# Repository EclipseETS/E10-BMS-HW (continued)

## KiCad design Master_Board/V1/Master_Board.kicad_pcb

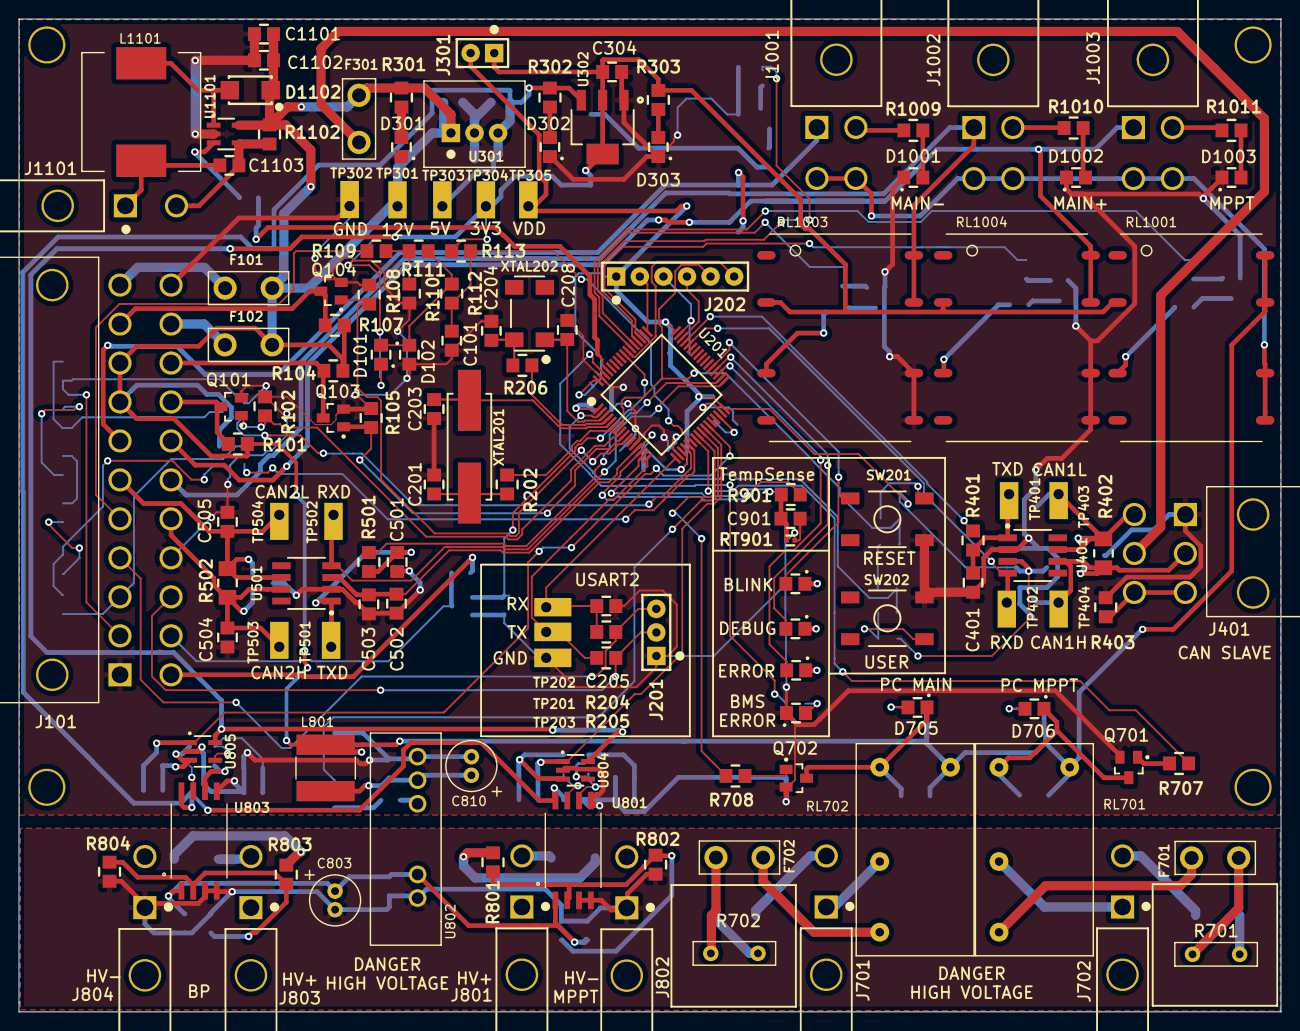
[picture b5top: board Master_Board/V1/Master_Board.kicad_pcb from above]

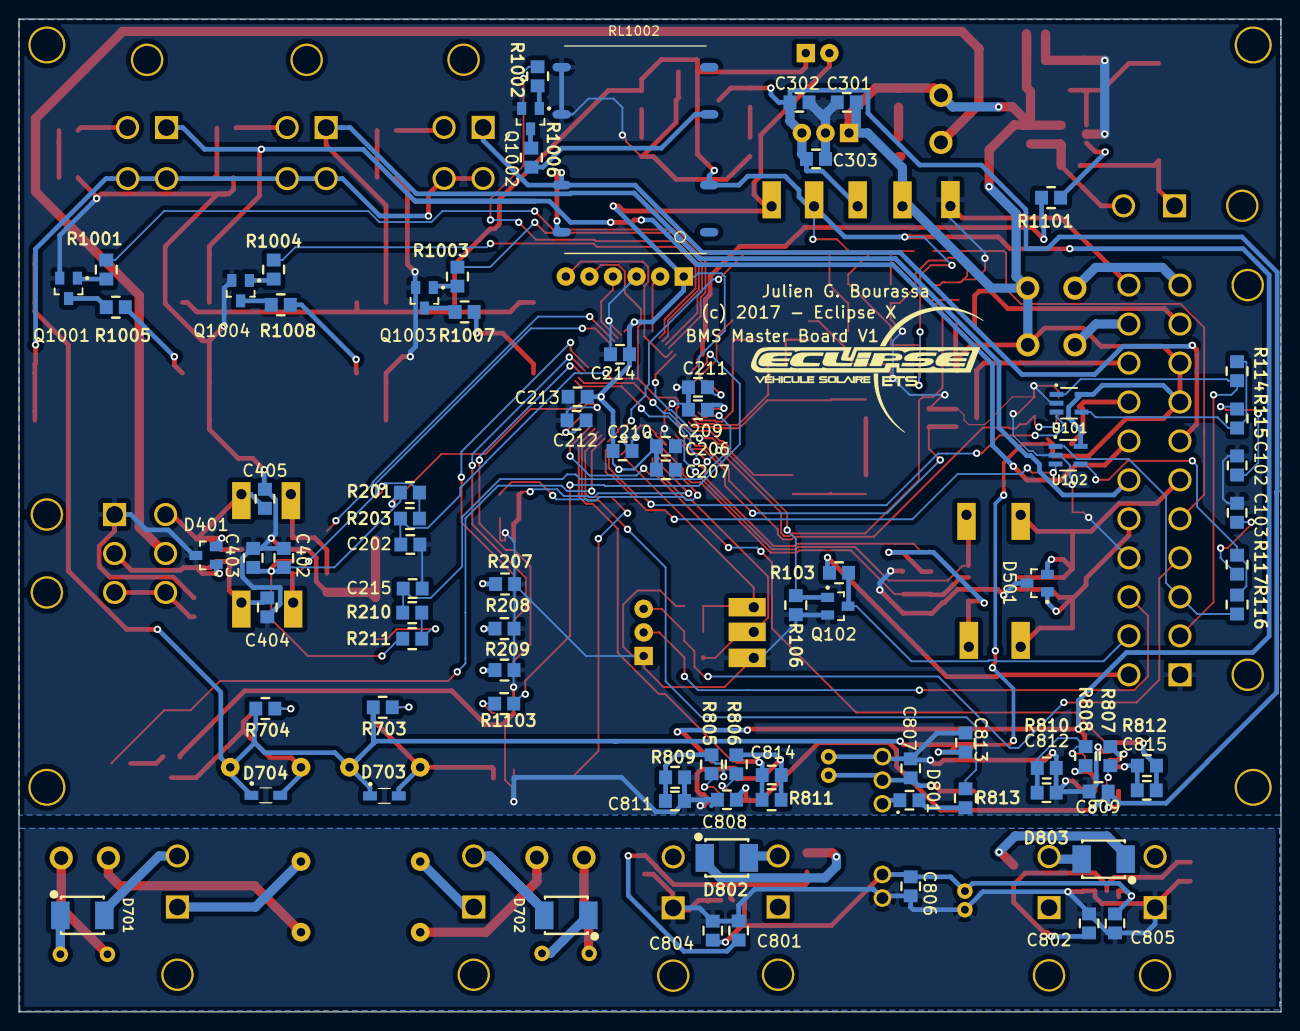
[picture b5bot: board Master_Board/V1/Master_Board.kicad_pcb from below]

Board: 2 copper layers, 136.0 x 107.0 mm, 217 parts (83 on the bottom side), 142 nets.

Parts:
C101, C207: 885012207092; C0805
C102, C103, C202, C210, C211, C213, C214, C215, C403, C503, C804, C805, C806, C807, C808, C809, C1102: 885012207098; C0805
C201, C203, C205, C404, C405, C504, C505: 885012007053; C0805
C204, C208: 885012007027; C0805
C206, C209, C402, C502, C901, C1103: 885012107015; C0805
C212, C301, C302, C1101: 885012107018; C0805
C303: 885012107014; C0805
C304: 885012107005; C0805
C401, C501, C801, C802, C811, C812, C814, C815: 885012207080; C0805
C803, C810: 860020472006; Radial-Can-5_11_2
C813: 885012207075; C0805
D101, D102, D801: SD0805S020S1R0; Diode_0805
D201, D301, D302, D303, D705, D706, D1001, D1002, D1003: 150080VS75000; LED_0805_GREEN
D202: 150080YS75000; LED_0805_YELLOW
D203, D1101: 150080RS75000; LED_0805_RED
D401, D501: D1213A-02SOL-7; SOT-23-3
D701, D702, D802, D803: NRVBS3200T3G; DO-214AA_SMB
D703, D704: NSR0530HT1G; SOD-323
D1102: B240AQ-13-F; DO-214AC_SMA
F101, F102: 39505000440; TE5_395
F301: 39511000440; TE5_395
F701, F702: 80812000440; TE5_395
J101: 649022227222
J201: Header_Male_Pin_2.54mm_1X3_,_Unshrouded; Headers_2.54mm_1X3
J202: Header_Male_Pin_2.54mm_1X6_,_Unshrouded; Headers_2.54mm_1X6
J301: Header_Male_Pin_2.54mm_1X2_,_Unshrouded; Headers_2.54mm_1X2
J401: 649006227222
J701, J702, J801, J802, J803, J804, J1101: 649002227222
J1001, J1002, J1003: 649004227222
L801: 744052471; WE-TPC-SMD
L1101: 7447715330; IND_1245
Q101, Q103, Q104: BSS806NH6327XTSA1; SOT-23-3
Q102: 2N7002P,215; SOT-23-3
Q701, Q702, Q1001, Q1002, Q1003, Q1004: BC849BLT1G; SOT-23-3
R101, R104, R107, R203, R210, R401, R501: RC0805JR-07100RL; R0805
R102, R105, R106, R108, R113: RC0805JR-07100KL; R0805
R103, R1103: RC0805JR-07330RL; R0805
R109: RC0805JR-072KL; R0805
R110: RC0805JR-07680RL; R0805
R111: RC0805JR-0710RL; R0805
R112, R205, R302, R703, R704, R1009, R1010, R1011, R1101: RC0805JR-071KL; R0805
R114, R115, R116, R117, R202, R206, R403: RC0805JR-070RL; R0805
R201, R204, R211, R301: RC0805JR-074K7L; R0805
R207, R208, R209, R303, R813: RC0805JR-07470RL; R0805
R402, R502: RC1206JR-07120RL; R1206
R701, R702: TR50JBC100R; TR50
R707, R708, R802, R804, R805, R806, R807, R808, R1001, R1002, R1003, R1004: RC0805JR-0710KL; R0805
R801, R803: RC0805JR-071ML; R0805
R809, R810, R811, R812: RC0805JR-0715KL; R0805
R901: RC0805JR-0733KL; R0805
R1005, R1006, R1007, R1008: RC0805JR-072K2L; R0805
R1102: RL0805FR-070R15L; R0805
RL701, RL702: ALQ312
RL1001, RL1002, RL1003, RL1004: CPC1907B
RT901: NCP15WB473F03RC; R0402
SW201, SW202: PTS645SM43SMTR92; PTS645_6X6X4_SMD
TP201, TP202, TP203, TP301, TP302, TP303, TP304, TP305, TP401, TP402, TP403, TP404, TP501, TP502, TP503, TP504: Test_Point_THM; Keystone_5001
U101, U102, U804, U805: LMV321RILT; SOT-23-5
U201: STM32F446RE; LQFP-64
U301: OKI-78SR-5/1.5-W36-C; OKI-78SR_Vertical
U302: AZ1117IH-3.3TRG1; SOT-223-3
U401, U501: SN65HVD232DR; SOIC-8
U801, U803: ACPL-C87A-500E; SSO-8
U802: NCS1S2405SC
U1101: AL8807W5-7; SOT-23-5
XTAL201: ABLS-8.000MHZ-D-T; HC49_US
XTAL202: ABS25-32.768KHZ-6-T; ABS25

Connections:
3.3V: C304.2, D101.1, J301.1, R113.1, R303.2, RL1001.2, RL1002.2, RL1003.2, RL1004.2, TP304.1, U302.2, U302.4, U804.5, U805.5
5V: C302.2, C303.2, C808.2, C809.2, R302.2, TP303.1, U301.3, U302.3, U801.8, U803.8
12V: C301.2, C813.1, C1101.1, C1102.1, D703.1, D704.1, D1102.1, F101.2, F102.2, F301.2, J101.8, J101.9, L801.2, R101.1, R104.1, R107.1, R301.2, R703.1, R704.1, R1102.1, RL701.1, RL702.1, RL1001.7, RL1001.8, TP301.1, U101.5, U102.5, U301.1, U1101.5
/12V_IN1: F101.1, J101.11
/12V_IN2: F102.1, J101.21
/ANA1: J101.2, R114.1, U101.1
/ANA2: J101.3, R116.2, U102.1
/ANA_IN: J101.5, R109.1
/ANA_SUP: J101.12, R103.1
/CAN1/CAN_N: C404.1, D401.1, J401.2, R402.2, TP404.1, U401.6
/CAN1/CAN_P: C405.1, D401.2, J401.4, R402.1, TP403.1, U401.7
/CAN1/Shield1: J401.3, J401.6, R403.1
/CAN1_RX: TP402.1, U201.44, U401.4
/CAN1_TX: R401.1, U201.45
/CAN2_H: C504.1, D501.1, J101.16, R502.1, TP503.1, U501.7
/CAN2_L: C505.1, D501.2, J101.6, R502.2, TP504.1, U501.6
/CAN2_RX: TP502.1, U201.33, U501.4
/CAN2_TX: R501.1, U201.34
/IO1: J101.17, J1002.1, RL1003.7, RL1003.8
/IO2: J101.7, J1001.1, RL1002.7, RL1002.8
/IO3: J101.18, J1003.1, RL1004.7, RL1004.8
/IO5: J101.19, Q101.3, R101.2
/IO7: J101.20, Q103.3, R104.2
/IO8: J101.10, Q104.3, R107.2
/Isolated/VoltageSense/5V_ISO: C803.1, C804.2, C805.2, C806.1, U801.1, U802.6, U803.1
/Isolated/VoltageSense/BP-HV+: D803.1, R803.1
/Isolated/VoltageSense/MPPT-HV+: D802.1, R801.1
/NRST: C202.1, J202.5, R203.2, U201.7
/NTC_1_ADC: C901.1, R901.1, RT901.2, U201.15
/NTC_1_GPIO: R901.2, U201.14
/PA4: U101.3, U201.20
/PA5: U102.3, U201.21
/PA6: C101.1, R112.2, R113.2, U201.22
/PA7: R707.2, U201.23
/PB0: C814.1, R811.2, U201.26, U804.1
/PB1: C815.1, R812.2, U201.27, U805.1
/PB4: Q102.1, R106.2, U201.56
/PB8: R1101.2, U201.61
/PB9: R1103.2, U201.62
/PB14: D203.2, U201.35
/PB15: D202.2, U201.36
/PC0: Q101.1, R102.2, U201.8
/PC1: Q103.1, R105.2, U201.9
/PC2: Q104.1, R108.2, U201.10
/PC4: R708.2, U201.24
/PC5: R813.2, U201.25
/PC6: D201.2, U201.37
/PC10: R1004.1, U201.51
/PC11: R1002.1, U201.52
/PC12: R1003.1, U201.53
/PD2: R1001.1, U201.54
/PWM2_OUT: J101.13, Q102.3, R103.2
/RS232_RX: J101.4, J201.3, R204.1
/RS232_TX: J101.14, J201.2, R205.1
/STM32F446/PA2_TX: R205.2, TP201.1, U201.16
/STM32F446/PA3_RX: C205.2, R204.2, TP202.1, U201.17
/STM32F446/SWCLK: J202.2, U201.49
/STM32F446/SWDIO: J202.4, U201.46
/STM32F446/SWO: J202.6, U201.55
/STM32F446/USER_BTN: C215.1, R210.2, U201.2
/VBat: C209.2, U201.1
CAN_PWR: F301.1, J401.5
DGND: C101.2, C102.2, C103.2, C201.1, C202.2, C203.2, C204.1, C205.1, C206.1, C207.1, C208.2, C209.1, C210.2, C211.1, C212.1, C213.2, C214.2, C215.2, C301.1, C302.1, C303.1, C304.1, C401.1, C402.1, C403.1, C404.2, C405.2, C501.2, C502.1, C503.1, C504.2, C505.2, C801.2, C802.2, C803.2, C804.1, C805.1, C806.2, C807.2, C808.1, C809.1, C810.2, C811.1, C812.1, C813.2, C901.2, C1101.2, C1102.2, D102.2, D301.1, D302.1, D303.1, D401.3, D501.3, D1001.1, D1002.1, D1003.1, D1101.1, J101.1, J101.15, J101.22, J201.1, J202.3, J401.1, J802.1, J804.1, Q101.2, Q102.2, Q103.2, Q104.2, Q701.2, Q702.2, Q1001.2, Q1002.2, Q1003.2, Q1004.2, R102.1, R105.1, R106.1, R108.1, R110.2, R207.1, R208.1, R209.1, R403.2, R802.2, R804.2, R809.2, R810.2, RL1002.5, RL1002.6, RL1003.5, RL1003.6, RL1004.5, RL1004.6, RT901.1, SW201.4, SW202.3, TP203.1, TP302.1, U101.2, U102.2, U201.12, U201.18, U201.31, U201.47, U201.63, U301.2, U302.1, U401.2, U501.2, U801.3, U801.4, U801.5, U802.1, U802.7, U803.3, U803.4, U803.5, U804.2, U805.2, U1101.2
unnamed: C102.1, R115.2
unnamed: C103.1, R117.1
unnamed: C201.2, R202.2, XTAL201.1
unnamed: C203.1, U201.5, XTAL201.2
unnamed: C204.2, R206.2, XTAL202.4
unnamed: C208.1, U201.3, XTAL202.1
unnamed: C212.2, U201.30
unnamed: C401.2, R401.2, TP401.1, U401.1
unnamed: C501.1, R501.2, TP501.1, U501.1
unnamed: C801.1, R801.2, R802.1, U801.2
unnamed: C802.1, R803.2, R804.1, U803.2
unnamed: C807.1, C810.1, L801.1, U802.2
unnamed: C811.2, R806.2, R809.1, U804.4
unnamed: C812.2, R808.2, R810.1, U805.4
unnamed: C814.2, R805.2, R811.1, U804.3
unnamed: C815.2, R807.2, R812.1, U805.3
unnamed: C1103.1, J1101.2, R1102.2, U1101.4
unnamed: C1103.2, J1101.1, L1101.2
unnamed: D101.2, D102.1, R111.2, R112.1
unnamed: D201.1, R207.2
unnamed: D202.1, R208.2
unnamed: D203.1, R209.2
unnamed: D301.2, R301.1
unnamed: D302.2, R302.1
unnamed: D303.2, R303.1
unnamed: D701.1, R701.1
unnamed: D701.2, J702.2
unnamed: D702.1, R702.1
unnamed: D702.2, J701.2
unnamed: D703.2, D705.1, Q702.3, RL702.2
unnamed: D704.2, D706.1, Q701.3, RL701.2
unnamed: D705.2, R703.2
unnamed: D706.2, R704.2
unnamed: D801.1, U802.3
unnamed: D801.2, R813.1
unnamed: D802.2, J801.2
unnamed: D803.2, J803.2
unnamed: D1001.2, R1009.2
unnamed: D1002.2, R1010.2
unnamed: D1003.2, R1011.2
unnamed: D1101.2, R1103.1
unnamed: D1102.2, L1101.1, U1101.1
unnamed: F701.1, R701.2
unnamed: F701.2, RL701.4
unnamed: F702.1, R702.2
unnamed: F702.2, RL702.4
unnamed: J701.1, RL702.3
unnamed: J702.1, RL701.3
unnamed: J1001.2, R1009.1
unnamed: J1001.3, J1001.4, J1002.3, J1002.4, J1003.3, J1003.4, RL1001.5, RL1001.6
unnamed: J1002.2, R1010.1
unnamed: J1003.2, R1011.1
unnamed: Q701.1, R707.1
unnamed: Q702.1, R708.1
unnamed: Q1001.1, R1001.2
unnamed: Q1001.3, R1005.1
unnamed: Q1002.1, R1002.2
unnamed: Q1002.3, R1006.1
unnamed: Q1003.1, R1003.2
unnamed: Q1003.3, R1007.1
unnamed: Q1004.1, R1004.2
unnamed: Q1004.3, R1008.1
unnamed: R109.2, R110.1, R111.1
unnamed: R114.2, R115.1, U101.4
unnamed: R116.1, R117.2, U102.4
unnamed: R201.1, R203.1, SW201.2
unnamed: R202.1, U201.6
unnamed: R206.1, U201.4
unnamed: R210.1, R211.1, SW202.1
unnamed: R805.1, U801.7
unnamed: R806.1, U801.6
unnamed: R807.1, U803.7
unnamed: R808.1, U803.6
unnamed: R1005.2, RL1001.3
unnamed: R1006.2, RL1002.3
unnamed: R1007.2, RL1003.3
unnamed: R1008.2, RL1004.3
unnamed: R1101.1, U1101.3
VDD: C206.2, C207.2, C210.1, C211.2, C213.1, C214.1, C402.2, C403.2, C502.2, C503.2, J202.1, J301.2, R201.2, R211.2, TP305.1, U201.13, U201.19, U201.32, U201.48, U201.64, U401.3, U501.3

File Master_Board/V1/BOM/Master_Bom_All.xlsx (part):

Component | References | Description | Manufacturer | Manufacturer Part Number | Supplier | Supplier Part Number | Quantity Per PCB | Footprint
1 | C803 C810 | CAP ALUM 47UF 20% 25V RADIAL | Wurth Electronics Inc. | 860020472006 | Digikey | 732-8823-1-ND | 2 | Radial-Can-5_11_2
2 | C204 C208 | CAP CER 6.8PF 25V C0G/NP0 0805 | Wurth Electronics Inc. | 885012007027 | Digikey | 732-7826-1-ND | 2 | C0805
3 | C201 C203 C205 C404 C405 C504 C505 | CAP CER 22PF 50V C0G/NP0 0805 | Wurth Electronics Inc. | 885012007053 | Digikey | 732-7848-1-ND | 7 | C0805
4 | C304 | CAP CER 22UF 6.3V X5R 0805 | Wurth Electronics Inc. | 885012107005 | Digikey | 732-7616-1-ND | 1 | C0805
5 | C303 | CAP CER 10UF 16V X5R 0805 | Wurth Electronics Inc. | 885012007027 | Digikey | 732-7624-1-ND | 1 | C0805
6 | C206 C209 C402 C502 C901 C1103 | CAP CER 1UF 25V X5R 0805 | Wurth Electronics Inc. | 885012107015 | Digikey | 732-7625-1-ND | 6 | C0805
7 | C212 C301 C302 C1101 | CAP CER 4.7UF 25V X5R 0805 | Wurth Electronics Inc. | 885012107018 | Digikey | 732-7628-1-ND | 4 | C0805
8 | C813 | CAP CER 0.33UF 25V X7R 0805 | Wurth Electronics Inc. | 885012207075 | Digikey | 732-7669-1-ND | 1 | C0805
9 | C401 C501 C801 C802 C811 C812 C814 C815 | CAP CER 100PF 50V X7R 0805 | Wurth Electronics Inc. | 885012207080 | Digikey | 732-8062-1-ND | 8 | C0805
10 | C101 C207 | CAP CER 10000PF 50V X7R 0805 | Wurth Electronics Inc. | 885012207092 | Digikey | 732-8074-1-ND | 2 | C0805
11 | C102 C103 C202 C210 C211 C213 C214 C215 C403 C503 C804 C805 C806 C807 C808 C809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 | CAP CER 0.1UF 50V X7R 0805 | Wurth Electronics Inc. | 885012207098 | Digikey | 732-8080-1-ND | 17 | C0805
12 | D203 D1101 | LED RED CLEAR 0805 SMD | Wurth Electronics Inc. | 150080RS75000 | Digikey | 732-4984-1-ND | 2 | LED_0805_RED
13 | D201 D301 D302 D303 D705 D706 D1001 D1002 D1003 | LED GREEN CLEAR 0805 SMD | Wurth Electronics Inc. | 150080VS75000 | Digikey | 732-4986-1-ND | 9 | LED_0805_GREEN
14 | D202 | LED YELLOW CLEAR 0805 SMD | Wurth Electronics Inc. | 150080YS75000 | Digikey | 732-4987-1-ND | 1 | LED_0805_YELLOW
15 | D1102 | DIODE SCHOTTKY 40V 2A SMA | Diode Incorporated | B240AQ-13-F | Digikey | B240AQ-13-FDICT-ND | 1 | DO-214AC_SMA
16 | D401 D501 | TVS DIODE 3.3VWM 10VC SOT23 | Diodes Incorporated | D1213A-02SOL-7 | Digikey | D1213A-02SOL-7DICT-ND | 2 | SOT-23-3
17 | D701 D702 D802 D803 | DIODE SCHOTTKY 200V 3A SMB | ON Semiconductor | NRVBS3200T3G | Digikey | NRVBS3200T3GOSCT-ND | 4 | DO-214AA_SMB
18 | D703 D704 | DIODE SCHOTTKY 30V 500MA SOD323 | ON Semiconductor | NSR0530HT1G | Digikey | NSR0530HT1GOSCT-ND | 2 | SOD-323
19 | D101 D102 D801 | DIODE SCHOTTKY 20V 1A 0805 | AVX Corporation | SD0805S020S1R0 | Digikey | 478-7800-1-ND | 3 | Diode_0805
20 | F101 F102 | FUSE BOARD MNT 1A 125VAC RADIAL | Littelfuse Inc. | 39505000440 | Digikey | WK4341BK-ND | 2 | TE5_395
21 | F301 | FUSE HOLDER RADIAL 250V 6.3A PCB | Littelfuse Inc. | 56200001009 | Digikey | WK0009-ND | 1 | TE5_395
22 | F701 F702 | FUSE BOARD MNT 2A 250VAC 450VDC | Littelfuse Inc. | 80812000440 | Digikey | WK6289-ND | 2 | TE5_395
23 | J701 J702 J801 J802 J803 J804 J1101 | HEADER MALE DUAL ANGLE W/MNT 2P | Wurth Electronics Inc. | 649002227222 | Digikey | 732-1937-ND | 7 | 649002227222
24 | J1001 J1002 J1003 | HEADER MALE DUAL ANGLE W/MNT 4P | Wurth Electronics Inc. | 649004227222 | Digikey | 732-1938-ND | 3 | 649004227222
25 | J401 | HEADER MALE DUAL ANGLE W/MNT 6P | Wurth Electronics Inc. | 649006227222 | Digikey | 732-1939-ND | 1 | 649006227222
26 | J101 | HEADER MALE DUAL ANGLE W/MNT 22P | Wurth Electronics Inc. | 649022227222 | Digikey | 732-4785-ND | 1 | 649022227222
27 | J301 | Pin Male Single Row Pin Header Strip | Manufacturer | Manufacturer Part Number | Ebay | Pin Male Single Row Pin Header Strip | 1 | Headers_2.54mm_1X2
28 | J201 | Pin Male Single Row Pin Header Strip | Manufacturer | Manufacturer Part Number | Ebay | Pin Male Single Row Pin Header Strip | 1 | Headers_2.54mm_1X3
29 | J202 | Pin Male Single Row Pin Header Strip | Manufacturer | Manufacturer Part Number | Ebay | Pin Male Single Row Pin Header Strip | 1 | Headers_2.54mm_1X6
30 | L801 | FIXED IND 470UH 140MA 5.5 OHM | Wurth Electronics Inc. | 744052471 | Digikey | 732-3668-1-ND | 1 | WE-TPC-SMD
31 | L1101 | FIXED IND 33UH 2.3A 85 MOHM SMD | Wurth Electronics Inc. | 7447715330 | Digikey | 732-2196-6-ND | 1 | IND_1245
32 | Q102 | MOSFET N-CH 60V 0.36A SOT-23 | Nexperia USA Inc. | 2N7002P,215 | Digikey | 1727-4692-1-ND | 1 | SOT-23-3
33 | Q701 Q702 Q1001 Q1002 Q1003 Q1004 | TRANS NPN 30V 0.1A SOT-23 | ON Semiconductor | BC849BLT1G | Digikey | BC849BLT1GOSCT-ND | 6 | SOT-23-3
34 | Q101 Q103 Q104 | MOSFET N-CH 20V 2.3A SOT23 | Infineon Technologies | BSS806NH6327XTSA1 | Digikey | BSS806NH6327XTSA1CT-ND | 3 | SOT-23-3
35 | R114 R115 R116 R117 R202 R206 R403 | RES SMD 0.0 OHM JUMPER 1/8W 0805 | Yageo | RC0805JR-070RL | Digikey | 311-0.0ARCT-ND | 7 | R0805
36 | R102 R105 R106 R108 R113 | RES SMD 100K OHM 5% 1/8W 0805 | Yageo | RC0805JR-07100KL | Digikey | 311-100KARCT-ND | 5 | R0805
37 | R101 R104 R107 R203 R210 R401 R501 | RES SMD 100 OHM 5% 1/8W 0805 | Yageo | RC0805JR-07100RL | Digikey | 311-100ARCT-ND | 7 | R0805
38 | R707 R708 R802 R804 R805 R806 R807 R808 R1001 R1002 R1003 R1004 | RES SMD 10K OHM 5% 1/8W 0805 | Yageo | RC0805JR-0710KL | Digikey | 311-10KARCT-ND | 12 | R0805
39 | R111 | RES SMD 10 OHM 5% 1/8W 0805 | Yageo | RC0805JR-0710RL | Digikey | 311-10ARCT-ND | 1 | R0805
40 | R809 R810 R811 R812 | RES SMD 15K OHM 5% 1/8W 0805 | Yageo | RC0805JR-0715KL | Digikey | 311-15KARTR-ND | 4 | R0805
41 | R112 R205 R302 R703 R704 R1009 R1010 R1011 R1101 | RES SMD 1K OHM 5% 1/8W 0805 | Yageo | RC0805JR-071KL | Digikey | 311-1.0KARCT-ND | 9 | R0805
42 | R801 R803 | RES SMD 1M OHM 5% 1/8W 0805 | Yageo | RC0805JR-071ML | Digikey | 311-1.0MARCT-ND | 2 | R0805
43 | R1005 R1006 R1007 R1008 | RES SMD 2.2K OHM 5% 1/8W 0805 | Yageo | RC0805JR-072K2L | Digikey | 311-2.2KARCT-ND | 4 | R0805
44 | R109 | RES SMD 2K OHM 5% 1/8W 0805 | Yageo | RC0805JR-072KL | Digikey | 311-2.0KARCT-ND | 1 | R0805
45 | R103 R1103 | RES SMD 330 OHM 5% 1/8W 0805 | Yageo | RC0805JR-07330RL | Digikey | 311-330ARCT-ND | 2 | R0805
46 | R901 | RES SMD 33K OHM 5% 1/8W 0805 | Yageo | RC0805JR-0733KL | Digikey | 311-33KARCT-ND | 1 | R0805
47 | R207 R208 R209 R303 R813 | RES SMD 470 OHM 5% 1/8W 0805 | Yageo | RC0805JR-07470RL | Digikey | 311-470ARCT-ND | 5 | R0805
48 | R201 R204 R211 R301 | RES SMD 4.7K OHM 5% 1/8W 0805 | Yageo | RC0805JR-074K7L | Digikey | 311-4.7KARCT-ND | 4 | R0805
49 | R110 | RES SMD 680 OHM 5% 1/8W 0805 | Yageo | RC0805JR-07680RL | Digikey | 311-680ARCT-ND | 1 | R0805
50 | R402 R502 | RES SMD 120 OHM 5% 1/4W 1206 | Yageo | RC1206JR-07120RL | Digikey | 311-120ERCT-ND | 2 | R1206
51 | R1102 | RES SMD 0.15 OHM 1% 1/8W 0805 | Yageo | RL0805FR-070R15L | Digikey | 311-.15SCT-ND | 1 | R0805
52 | R701 R702 | RES 100 OHM 50W 5% TO220 | Stackpole Electronics Inc. | TR50JBC100R | Digikey | TR50JBC100R-ND | 2 | TR50
53 | RL701 RL702 | RELAY GEN PURPOSE SPST 10A 12V | Panasonic Electric Works | ALQ312 | Digikey | 255-3556-ND | 2 | ALQ312
54 | RL1001 RL1002 RL1003 RL1004 | RELAY OPTOMOS SP-NO 6A 8-SOP | IXYS Integrated Circuits Division | CPC1907B | Digikey | CLA394-ND | 4 | CPC1907B
55 | RT901 | NTC THERMISTOR 47K OHM 1% 0402 | Murata Electronics North America | NCP15WB473F03RC | Digikey | 490-4802-1-ND | 1 | R0402
56 | SW201 SW202 | SWITCH TACTILE SPST-NO 0.05A 12V | C&K | PTS645SM43SMTR92 LFS | Digikey | CKN9112CT-ND | 2 | PTS645_6X6X4_SMD
57 | U801 U803 | Precision Optically Isolated Voltage Sensor | Broadcom Limited | ACPL-C87A-500E | Digikey | 516-3140-1-ND | 2 | SSO-8
58 | U1101 | IC LED DRVR REG PWM 1A TSOT25 | Diodes Incorporated | AL8808WT-7 | Digikey | AL8808WT-7DICT-ND | 1 | SOT-23-5
59 | U302 | IC REG LDO 3.3V 0.8A SOT223 | Diodes Incorporated | AZ1117IH-3.3TRG1 | Digikey | AZ1117IH-3.3TRG1DICT-ND | 1 | SOT-223-3
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
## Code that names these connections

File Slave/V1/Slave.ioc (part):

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Mcu.Name=STM32F446R(C-E)Tx
Mcu.Package=LQFP64
Mcu.UserName=STM32F446RETx
PA0-WKUP.GPIOParameters=GPIO_Label
PA0-WKUP.GPIO_Label=NTC_1_ADC
PA0-WKUP.Signal=ADCx_IN0
PA1.GPIOParameters=GPIO_Label
PA1.GPIO_Label=NTC_1_EN
PA1.Signal=GPIO_Output
PA10.GPIOParameters=GPIO_Label
PA10.GPIO_Label=CS_8
PA10.Signal=GPIO_Output
PA13.GPIOParameters=GPIO_Label
PA13.GPIO_Label=TMS
PA13.Signal=SYS_JTMS-SWDIO
PA14.GPIOParameters=GPIO_Label
PA14.GPIO_Label=TCK
PA14.Signal=SYS_JTCK-SWCLK
PA15.GPIOParameters=GPIO_Label
PA15.GPIO_Label=DE_1
PA15.Signal=GPIO_Output
PA2.GPIOParameters=GPIO_Label
PA2.GPIO_Label=USART_TX
PA2.Mode=Asynchronous
PA2.Signal=USART2_TX
PA3.GPIOParameters=GPIO_Label
PA3.GPIO_Label=USART_RX
PA3.Mode=Asynchronous
PA3.Signal=USART2_RX
PA5.GPIOParameters=GPIO_Label
PA5.GPIO_Label=LED_BLINK
PA5.Signal=GPIO_Output
PA6.GPIOParameters=GPIO_Label
PA6.GPIO_Label=LED_DEBUG
PA6.Signal=GPIO_Output
PA7.GPIOParameters=GPIO_Label
PA7.GPIO_Label=LED_ERROR
PA7.Signal=GPIO_Output
PA8.GPIOParameters=GPIO_Label
PA8.GPIO_Label=POWER_EN
PA8.Signal=GPIO_Output
PA9.GPIOParameters=GPIO_Label
PA9.GPIO_Label=DE_8
PA9.Signal=GPIO_Output
PB0.GPIOParameters=GPIO_Label
PB0.GPIO_Label=NTC_2_EN
PB0.Signal=GPIO_Output
PB1.GPIOParameters=GPIO_Label
PB1.GPIO_Label=NTC_2_ADC
PB1.Signal=ADCx_IN9
PB10.GPIOParameters=GPIO_Label
PB10.GPIO_Label=CS_5
PB10.Signal=GPIO_Output
PB12.GPIOParameters=GPIO_Label
PB12.GPIO_Label=DE_6
PB12.Signal=GPIO_Output
PB13.GPIOParameters=GPIO_Label
PB13.GPIO_Label=CS_6
PB13.Signal=GPIO_Output
PB14.GPIOParameters=GPIO_Label
PB14.GPIO_Label=DE_7
PB14.Signal=GPIO_Output
PB15.GPIOParameters=GPIO_Label
PB15.GPIO_Label=CS_7
PB15.Signal=GPIO_Output
PB2.GPIOParameters=GPIO_Label
PB2.GPIO_Label=DE_5
PB2.Signal=GPIO_Output
PB3.GPIOParameters=GPIO_Label
PB3.GPIO_Label=SWO
PB3.Signal=SYS_JTDO-SWO
PB4.GPIOParameters=GPIO_Label
PB4.GPIO_Label=CS_2
PB4.Signal=GPIO_Output
PB6.GPIOParameters=GPIO_Label
PB6.GPIO_Label=BALANCING_PWM_5
PB6.Signal=S_TIM4_CH1
PB7.GPIOParameters=GPIO_Label
PB7.GPIO_Label=BALANCING_PWM_6
PB7.Signal=S_TIM4_CH2
PB8.GPIOParameters=GPIO_Label
PB8.GPIO_Label=BALANCING_PWM_7
PB8.Signal=S_TIM4_CH3
PB9.GPIOParameters=GPIO_Label
PB9.GPIO_Label=BALANCING_PWM_8
PB9.Signal=S_TIM4_CH4
PC0.GPIOParameters=GPIO_Label
PC0.GPIO_Label=DE_3
PC0.Signal=GPIO_Output
PC1.GPIOParameters=GPIO_Label
PC1.GPIO_Label=CS_3
PC1.Signal=GPIO_Output
PC10.Mode=RX_Only_Simplex_Unidirect_Master
PC10.Signal=SPI3_SCK
PC11.Mode=RX_Only_Simplex_Unidirect_Master
PC11.Signal=SPI3_MISO
PC12.GPIOParameters=GPIO_Label
PC12.GPIO_Label=CS_1
PC12.Signal=GPIO_Output
PC13.GPIOParameters=GPIO_Label,GPIO_ModeDefaultEXTI
PC13.GPIO_Label=BTN_USER
PC13.GPIO_ModeDefaultEXTI=GPIO_MODE_EVT_RISING
PC13.Signal=GPXTI13
PC14-OSC32_IN.Signal=RCC_OSC32_IN
PC15-OSC32_OUT.Signal=RCC_OSC32_OUT
PC2.GPIOParameters=GPIO_Label
PC2.GPIO_Label=DE_4
PC2.Signal=GPIO_Output
PC3.GPIOParameters=GPIO_Label
PC3.GPIO_Label=CS_4
PC3.Signal=GPIO_Output
PC6.GPIOParameters=GPIO_Label
PC6.GPIO_Label=BALANCING_PWM_1
PC6.Signal=S_TIM8_CH1
PC7.GPIOParameters=GPIO_Label
PC7.GPIO_Label=BALANCING_PWM_2
PC7.Signal=S_TIM8_CH2
PC8.GPIOParameters=GPIO_Label
PC8.GPIO_Label=BALANCING_PWM_3
PC8.Signal=S_TIM8_CH3
PC9.GPIOParameters=GPIO_Label
PC9.GPIO_Label=BALANCING_PWM_4
PC9.Signal=S_TIM8_CH4
PD2.GPIOParameters=GPIO_Label
PD2.GPIO_Label=DE_2
PD2.Signal=GPIO_Output
PH0-OSC_IN.Mode=HSE-External-Oscillator
PH0-OSC_IN.Signal=RCC_OSC_IN
PH1-OSC_OUT.Mode=HSE-External-Oscillator
PH1-OSC_OUT.Signal=RCC_OSC_OUT
RCC.HSE_VALUE=8000000
RCC.SYSCLKFreq_VALUE=180000000
RCC.SYSCLKSource=RCC_SYSCLKSOURCE_PLLCLK
board=NUCLEO-F446RE
boardIOC=true

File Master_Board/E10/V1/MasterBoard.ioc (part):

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Mcu.Name=STM32F446R(C-E)Tx
Mcu.Package=LQFP64
Mcu.UserName=STM32F446RETx
PA0-WKUP.Signal=GPIO_Output
PA1.Signal=ADCx_IN1
PA11.Mode=Master
PA11.Signal=CAN1_RX
PA12.Mode=Master
PA12.Signal=CAN1_TX
PA13.Signal=SYS_JTMS-SWDIO
PA14.Signal=SYS_JTCK-SWCLK
PA2.Signal=USART2_TX
PA3.Signal=USART2_RX
PA4.Signal=COMP_DAC1_group
PA5.Signal=COMP_DAC2_group
PA6.Signal=ADCx_IN6
PA7.Signal=GPIO_Output
PB0.Signal=ADCx_IN8
PB1.Signal=ADCx_IN9
PB12.Mode=Slave
PB12.Signal=CAN2_RX
PB13.Mode=Slave
PB13.Signal=CAN2_TX
PB14.Signal=GPIO_Output
PB15.Signal=GPIO_Output
PB3.Signal=SYS_JTDO-SWO
PB4.Signal=S_TIM3_CH1
PB8.Signal=S_TIM10_CH1
PB9.Signal=GPIO_Output
PC0.Signal=GPIO_Output
PC1.Signal=GPIO_Output
PC10.Signal=GPIO_Output
PC11.Signal=GPIO_Output
PC12.Signal=GPIO_Output
PC13.Signal=GPIO_Input
PC14-OSC32_IN.Signal=RCC_OSC32_IN
PC15-OSC32_OUT.Signal=RCC_OSC32_OUT
PC2.Signal=GPIO_Output
PC4.Signal=GPIO_Output
PC5.Signal=GPIO_Output
PC6.Signal=GPIO_Output
PD2.Signal=GPIO_Output
PH0-OSC_IN.Signal=RCC_OSC_IN
PH1-OSC_OUT.Signal=RCC_OSC_OUT

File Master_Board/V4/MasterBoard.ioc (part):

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Mcu.Name=STM32F446R(C-E)Tx
Mcu.Package=LQFP64
Mcu.UserName=STM32F446RETx
PA0-WKUP.GPIOParameters=GPIO_Label
PA0-WKUP.GPIO_Label=NTC_1_GPIO
PA0-WKUP.Signal=GPIO_Output
PA1.GPIOParameters=GPIO_Label
PA1.GPIO_Label=NTC_1_ADC
PA1.Signal=ADCx_IN1
PA10.Mode=Asynchronous
PA10.Signal=USART1_RX
PA11.Mode=Master
PA11.Signal=CAN1_RX
PA12.Mode=Master
PA12.Signal=CAN1_TX
PA13.Signal=SYS_JTMS-SWDIO
PA14.Signal=SYS_JTCK-SWCLK
PA2.Mode=Asynchronous
PA2.Signal=USART2_TX
PA3.Mode=Asynchronous
PA3.Signal=USART2_RX
PA4.GPIOParameters=GPIO_Label
PA4.GPIO_Label=VSENSE_BP
PA4.Signal=ADCx_IN4
PA5.GPIOParameters=GPIO_Label
PA5.GPIO_Label=VSENSE_EN
PA5.Signal=GPIO_Output
PA6.GPIOParameters=GPIO_Label
PA6.GPIO_Label=VSENSE_MPPT
PA6.Signal=ADCx_IN6
PA9.Mode=Asynchronous
PA9.Signal=USART1_TX
PB10.GPIOParameters=GPIO_Label
PB10.GPIO_Label=PC_MAIN
PB10.Signal=GPIO_Output
PB12.GPIOParameters=GPIO_Label
PB12.GPIO_Label=LEDDRIVER_ERROR
PB12.Signal=GPIO_Output
PB13.Mode=Slave
PB13.Signal=CAN2_TX
PB14.GPIOParameters=GPIO_Label
PB14.GPIO_Label=LED_ASSERT
PB14.Signal=GPIO_Output
PB15.GPIOParameters=GPIO_Label
PB15.GPIO_Label=LED_DEBUG
PB15.Signal=GPIO_Output
PB2.GPIOParameters=GPIO_Label
PB2.GPIO_Label=PC_MPPT
PB2.Signal=GPIO_Output
PB3.Signal=SYS_JTDO-SWO
PB5.Mode=Slave
PB5.Signal=CAN2_RX
PC0.GPIOParameters=GPIO_Label
PC0.GPIO_Label=GPO1_EN
PC0.Signal=GPIO_Output
PC1.GPIOParameters=GPIO_Label
PC1.GPIO_Label=GP02_EN
PC1.Signal=GPIO_Output
PC10.GPIOParameters=GPIO_Label
PC10.GPIO_Label=CONTACTOR_MPPT
PC10.Signal=GPIO_Output
PC11.GPIOParameters=GPIO_Label
PC11.GPIO_Label=CONTACTOR_MAINN
PC11.Signal=GPIO_Output
PC12.GPIOParameters=GPIO_Label
PC12.GPIO_Label=CONTACTOR_MAINP
PC12.Signal=GPIO_Output
PC14-OSC32_IN.Signal=RCC_OSC32_IN
PC15-OSC32_OUT.Signal=RCC_OSC32_OUT
PC2.GPIOParameters=GPIO_Label
PC2.GPIO_Label=GPO3_EN
PC2.Signal=GPIO_Output
PC6.GPIOParameters=GPIO_Label
PC6.GPIO_Label=LED_BLINK
PC6.Signal=GPIO_Output
PD2.GPIOParameters=GPIO_Label
PD2.GPIO_Label=CONTACTOR_HIGHSIDE
PD2.Signal=GPIO_Output
PH0-OSC_IN.Signal=RCC_OSC_IN
PH1-OSC_OUT.Signal=RCC_OSC_OUT

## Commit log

2017-06-08 add gitignore
2017-06-08 Start sch of slave
2017-06-08 clear annotation
2017-06-08 add notes
2017-06-08 add LED to reverse protection + balancing
2017-06-11 placing components
2017-06-11 Add file Master_Board
2017-06-11 placing component on front end
2017-06-11 adding 8 front end
2017-06-11 placed front end 1 to 5
2017-06-11 placed front end nb 8
2017-06-12 front end done
2017-06-12 place connector
2017-06-12 Add Master_Board files
2017-06-15 Place front end to fit battery pack
2017-06-16 Routing signals
2017-06-16 Routing signals 2
2017-06-17 Routing done, DRC almost clean
2017-06-17 add cutout next to crystals, DRC clean
2017-06-17 DRC Clean
2017-06-17 add capacitor to Temperature reading
2017-06-17 Add Master_Board modules
2017-06-18 add SWD silkscreen
2017-06-18 add silkscreen USART2
2017-06-18 add picture front and back
2017-06-18 ioc: add spi3_mosi and set pwm mode for tim8 channels
2017-06-18 generate gerber
2017-06-18 git modify Master_board
2017-06-19 Add filter in VoltageSense
2017-06-21 fix library LED issue
2017-06-21 Add page LedDriver
2017-06-21 schematic small fix
2017-06-21 Modify MasterBoard.sch
2017-06-21 Modify pinout in MasterBoard.ioc
2017-06-23 Add page LEDDriver.sch
2017-06-23 Add Master_Board.net
2017-06-23 Create Master board PCB
2017-06-26 Modify Master_board PCB
2017-06-26 Routing Master PCB
2017-06-27 add resistor to op amp power
2017-06-27 update component
2017-06-27 Routing BmsMasterBoard
2017-06-28 add comment
2017-06-28 Release1 MasterBoard PCB
2017-06-29 Fix some routing on MasterBoard
2017-07-03 Move precharge resistor
2017-07-03 Modify silk screen
2017-07-03 remove lib-rescue
2017-07-03 Add polarity safety
2017-07-03 Modify schematic wire in precharge
2017-07-03 Fix Master .pro header
2017-07-03 Add gain in analog out
2017-07-03 Generate Gerber files
2017-07-03 Add gerber files .zip
2017-07-04 add Slave BOM
2017-07-04 start to place pin on uC
2017-07-04 Generate BOM for slave and master
2017-07-05 placing power supply
2017-07-05 remove NTC, place component on PCB
2017-07-05 routing uC
2017-07-05 board done, DRC clean
2017-07-06 minor fix
2017-07-10 Add Current Sense BOM
2017-07-10 Add bom for digikey/wurth
2017-07-18 Add Master_Bom_All
2017-07-18 Modify Master_Bom_All
2017-07-20 add note
2017-07-20 minor
2017-08-02 Added V2 of Master Board
2017-08-05 Add comment for V2
2017-08-22 add comment with new ADC RC filter values
2017-08-22 Update Slave ioc file
2017-08-22 Changed CAN to CAN2, add LED ID
2017-08-22 add drill map
2017-08-22 Add Module and thermistor ID
2017-08-22 Add Eclipse Logo, generate Gerber
2017-08-22 Place part in PCB
2017-08-23 Move CAN to CAN2, Generate GERBER
2017-08-23 Fix funky trace, Generate GERBER
2017-08-23 Done placing parts on PCB
2017-08-29 Route small traces
2017-09-01 update gitignore
2017-09-06 Finish routing
2017-09-11 Add project preview
2017-11-02 Added BOM files
2017-11-10 update pdf
2018-02-14 schematic master V3
2018-02-18 Rooting Master V3
2018-02-18 Silkscreen Master V3
2018-02-18 Schematic was unsaved
2018-02-24 Correction of kill switch circuit
2018-04-13 Changed values of optocoupler resistor
2018-05-02 Add the do not install mark to the fan resistor
2018-08-02 add master V4 base on the V3
2018-08-02 Reparation of the fan circuit -no more patch require on the PSU
2018-09-20 Repair broken librairy references
2018-09-20 Add pull-up and connector to Master V4 circuit
2018-09-21 Remove big crappy connector and remap 12V
2018-09-21 Change name of schematic Fan Control
2018-09-21 clean schematic
2018-09-21 add usb schematic
2018-10-07 add negative contactor reading and start USB feature
2018-10-08 Add ESD Protection and filtering to the USB circuit
2018-10-08 add gpio to negative contactor reading
2018-10-27 Master V4 routed
2018-10-27 Repair USB ESD protection net
2018-10-27 Reanotate all schematic and finish routing
2018-10-27 Make E10 & E10.1 Folder for Master
2018-10-28 align fuse
2018-10-28 Add info silkscreen on the board
2018-10-29 Refresh footprint for newer 3D model
2018-11-10 Modification after review
2018-11-13 Beef that trace
2018-12-06 add Vusb_sense
2019-01-12 last minute change
2019-01-19 fix symbol mapping
2019-01-19 Generate Gerber and bom
2019-01-19 fix cristal, OKI-H, boot0, silk align and create BOM and gerber files
2019-04-20 patch problem of V1
2019-04-20 Routing of the patch
2019-05-10 Update repo
2019-05-10 Modification after review of @gabChouin - Gabriel Chouinard
2019-05-10 Replace mounting hole
2019-05-10 Little tweak for beauty reason
2019-05-31 Gerber Generation Master E10.1 V2
2019-12-04 BMS master board V3 added. Increased track width to allow more current for fans. No other major modifications.
2019-12-14 2 new fuses added. PCB traces overhaul to support more current. Some small layout changes.
2019-12-14 Minor adjustments to trace routes
2019-12-19 Block Diagram added in Documentation folder.
2020-01-15 Update based on peer review. Missing text added, block diagram fixed.
2020-01-25 Small layout adjustments for clarity and visibility.
2020-02-22 moved some vias
